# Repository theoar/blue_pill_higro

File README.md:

# blue_pill_higro

Simple higormeter based on DTH11 sensor and STM32 Blue Pill module.
Program uses non-block access to the sensor based on timer input capture interrupt.
Device build with STM32 LL libs.

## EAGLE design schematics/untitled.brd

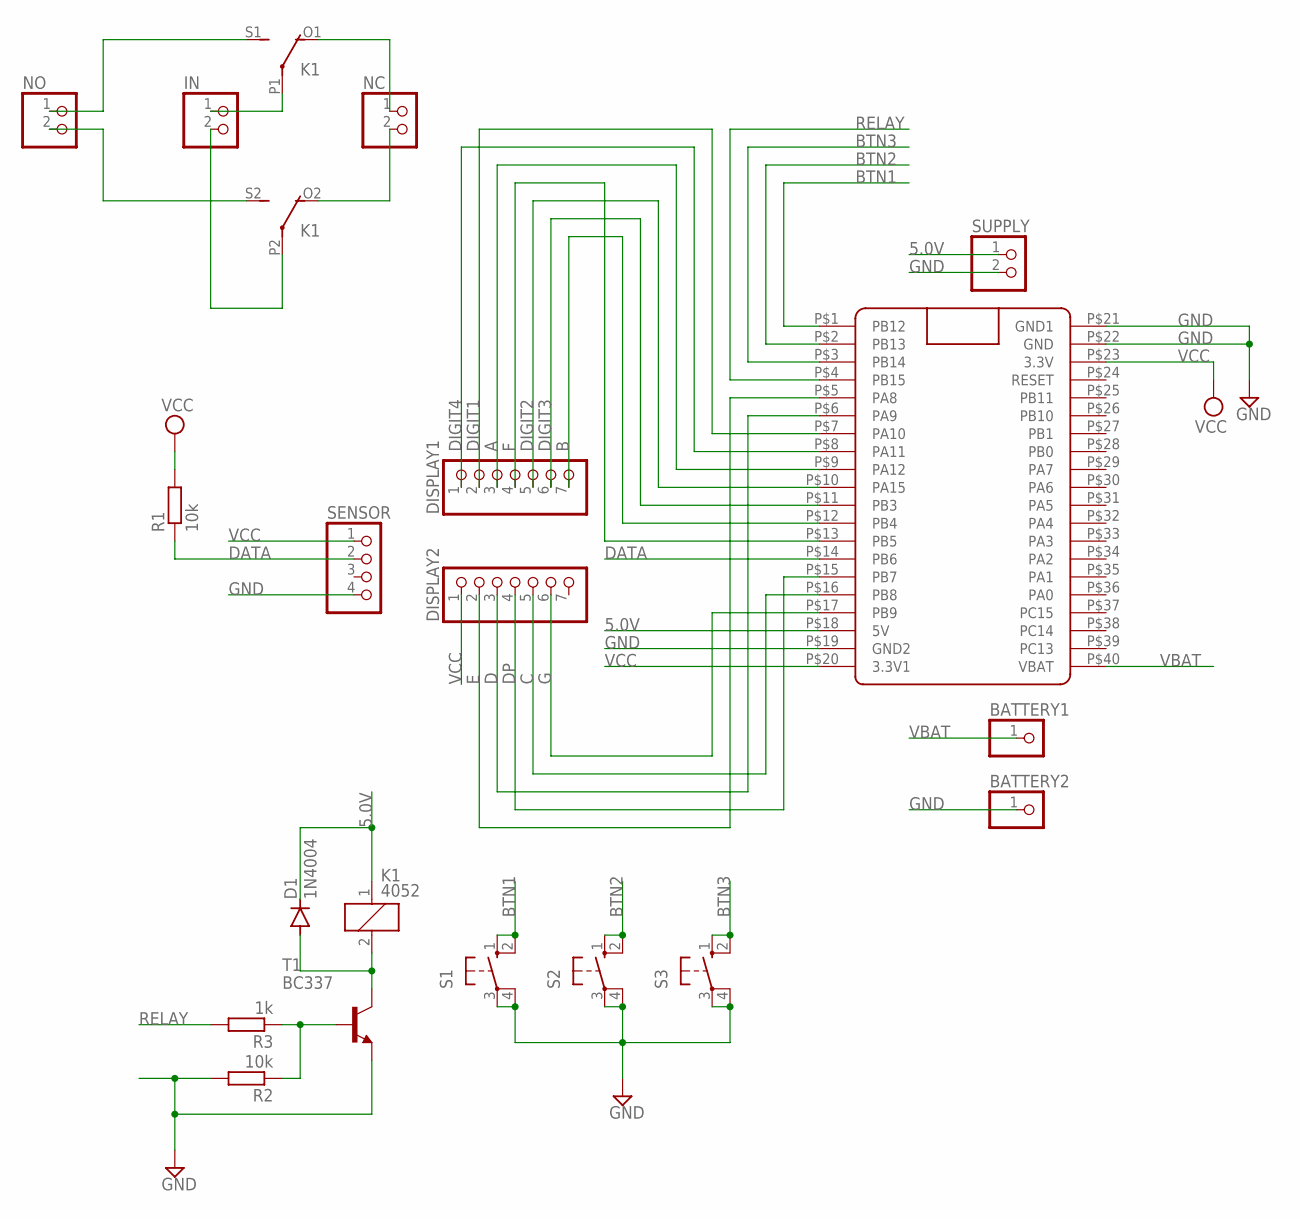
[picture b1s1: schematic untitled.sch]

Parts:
BATTERY1, BATTERY2: PINHD-1X1; 1X01
D1: 1N4004; DO41-10
DISPLAY1, DISPLAY2: PINHD-1X7; 1X07
IN: PINHD-1X2; 1X02
K1: 4052; F4052
NC: PINHD-1X2; 1X02
NO: PINHD-1X2; 1X02
R1, R2: 10k; 0207/10
R3: 1k; 0207/10
S1, S2, S3: 10-XX; B3F-10XX
SENSOR: PINHD-1X4; 1X04
SUPPLY: PINHD-1X2; 1X02
T1: BC337; TO92
U$1: BLUE_PILL

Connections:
5.0V: D1.C, K1.1, SUPPLY.1, U$1.P$18 (5V)
A: DISPLAY1.3, U$1.P$9 (PA12)
B: DISPLAY1.7, U$1.P$12 (PB4)
BTN1: S1.1 (S), S1.2 (S1), U$1.P$1 (PB12)
BTN2: S2.1 (S), S2.2 (S1), U$1.P$2 (PB13)
BTN3: S3.1 (S), S3.2 (S1), U$1.P$3 (PB14)
C: DISPLAY2.5, U$1.P$16 (PB8)
D: DISPLAY2.3, U$1.P$6 (PA9)
DATA: R1.1, SENSOR.2, U$1.P$14 (PB6)
DIGIT1: DISPLAY1.2, U$1.P$7 (PA10)
DIGIT2: DISPLAY1.5, U$1.P$10 (PA15)
DIGIT3: DISPLAY1.6, U$1.P$11 (PB3)
DIGIT4: DISPLAY1.1, U$1.P$8 (PA11)
DP: DISPLAY2.4, U$1.P$15 (PB7)
E: DISPLAY2.2, U$1.P$5 (PA8)
F: DISPLAY1.4, U$1.P$13 (PB5)
G: DISPLAY2.6, U$1.P$17 (PB9)
GND: BATTERY2.1, R2.2, S1.3, S1.4 (P1), S2.3, S2.4 (P1), S3.3, S3.4 (P1), SENSOR.4, SUPPLY.2, T1.1 (E), U$1.P$19 (GND2), U$1.P$21 (GND1), U$1.P$22 (GND)
unnamed: K1.O1 (O), NC.1
unnamed: K1.O2 (O), NC.2
unnamed: IN.2, K1.P2
unnamed: K1.S2 (S), NO.2
unnamed: D1.A, K1.2, T1.3 (C)
unnamed: R2.1, R3.1, T1.2 (B)
unnamed: IN.1, K1.P1
NO: K1.S1 (S), NO.1
RELAY: R3.2, U$1.P$4 (PB15)
VBAT: BATTERY1.1, U$1.P$40 (VBAT)
VCC: DISPLAY2.1, R1.2, SENSOR.1, U$1.P$20 (3.3V1), U$1.P$23 (3.3V)

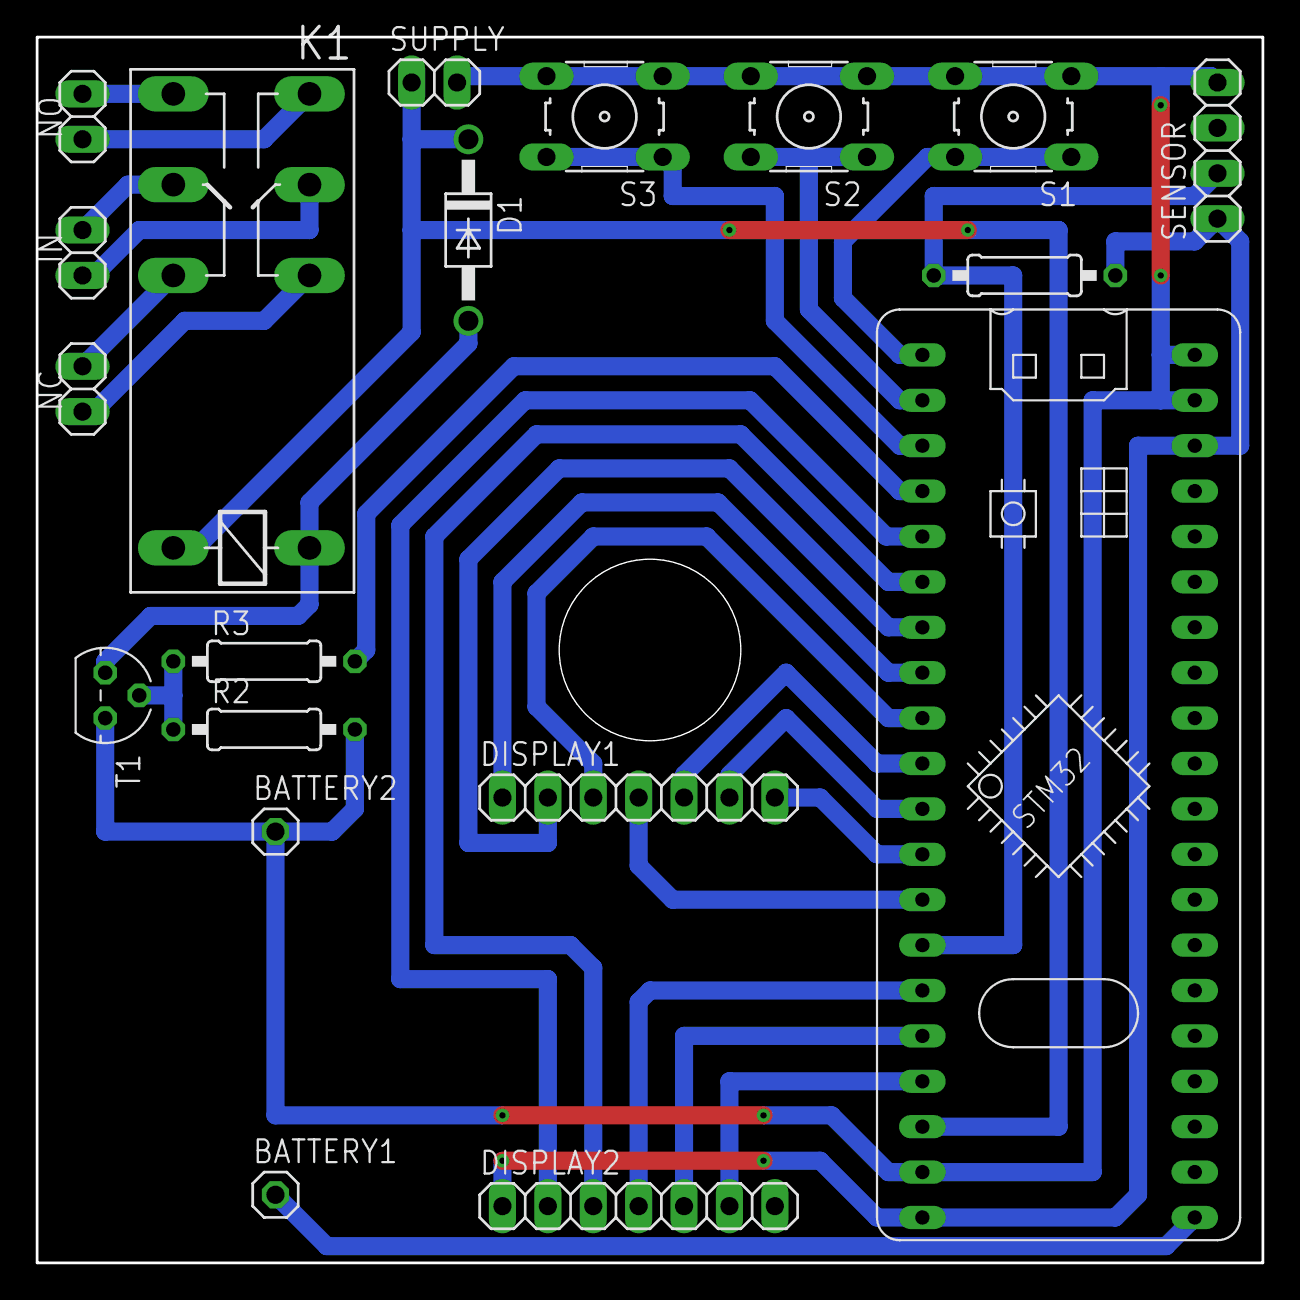
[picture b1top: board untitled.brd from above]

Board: 2 copper layers, 68.6 x 68.6 mm, 19 parts (0 on the bottom side), 29 nets.

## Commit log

2020-11-01 Update files with local repository
2020-11-09 Add algorithm logic to provide simple binary humidity regulator.
2020-11-12 Removed existing bugs.
2020-11-14 Fixed bug with frozen display.
2020-11-14 Create LICENSE
2020-12-13 Add following features:
2020-12-13 Add following features: -scroll for 7segment display -generic menu item with edit/display features -keyboard hadler for simple keys
2020-12-20 Fixed bugs, rewrite display handler.
2023-01-04 Humidity threshold now is depented on current temperature. The dependency is just simple linear function determinted by two points, where x=temperature and y=humidity-threshold.
2023-01-04 Added EAGEL schematics. WARNING - the schematic doesn't take into account changes in dht11 power pin. In current version the power pin is driven directly from MCU/
2023-01-08 Refactored parts of code; added new functions
